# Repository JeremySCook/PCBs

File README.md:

# PCBs
Circuit boards designed by Jeremy Cook

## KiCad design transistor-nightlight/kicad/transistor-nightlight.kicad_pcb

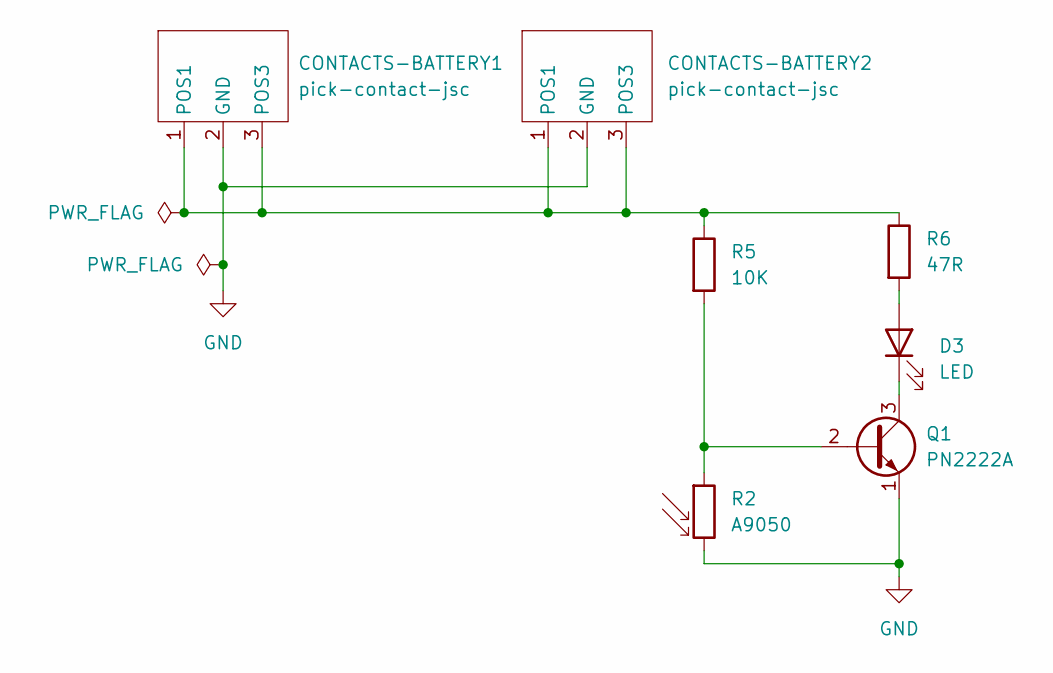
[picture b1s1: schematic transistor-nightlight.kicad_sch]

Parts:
CONTACTS-BATTERY1, CONTACTS-BATTERY2: pick-contact-jsc; pick-battery-jsc
D3: LED; LED_D3.0mm
Q1: PN2222A; TO-92_Inline
R2: A9050; R_LDR_5.0x4.1mm_P3mm_Vertical
R5: 10K; R_Axial_DIN0204_L3.6mm_D1.6mm_P2.54mm_Vertical
R6: 47R; R_Axial_DIN0204_L3.6mm_D1.6mm_P2.54mm_Vertical

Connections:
GND: CONTACTS-BATTERY1.2 (GND), CONTACTS-BATTERY2.2 (GND), Q1.1 (E), R2.2
unnamed: CONTACTS-BATTERY1.1 (POS1), CONTACTS-BATTERY1.3 (POS3), CONTACTS-BATTERY2.1 (POS1), CONTACTS-BATTERY2.3 (POS3), R5.1, R6.1
unnamed: D3.2 (A), R6.2
unnamed: D3.1 (K), Q1.3 (C)
unnamed: Q1.2 (B), R2.1, R5.2

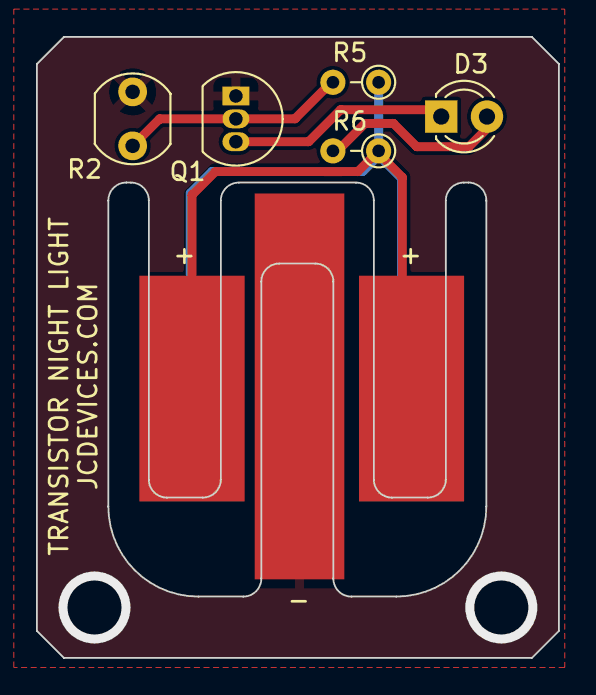
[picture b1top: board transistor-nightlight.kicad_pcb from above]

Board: 2 copper layers, 29.0 x 34.5 mm, 7 parts (1 on the bottom side), 5 nets.

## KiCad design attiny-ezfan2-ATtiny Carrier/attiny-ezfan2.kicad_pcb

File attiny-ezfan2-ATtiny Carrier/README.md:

Simple ATtiny85/45/25 breakout

Originally available on Tindie: https://www.tindie.com/products/27207 - now retired

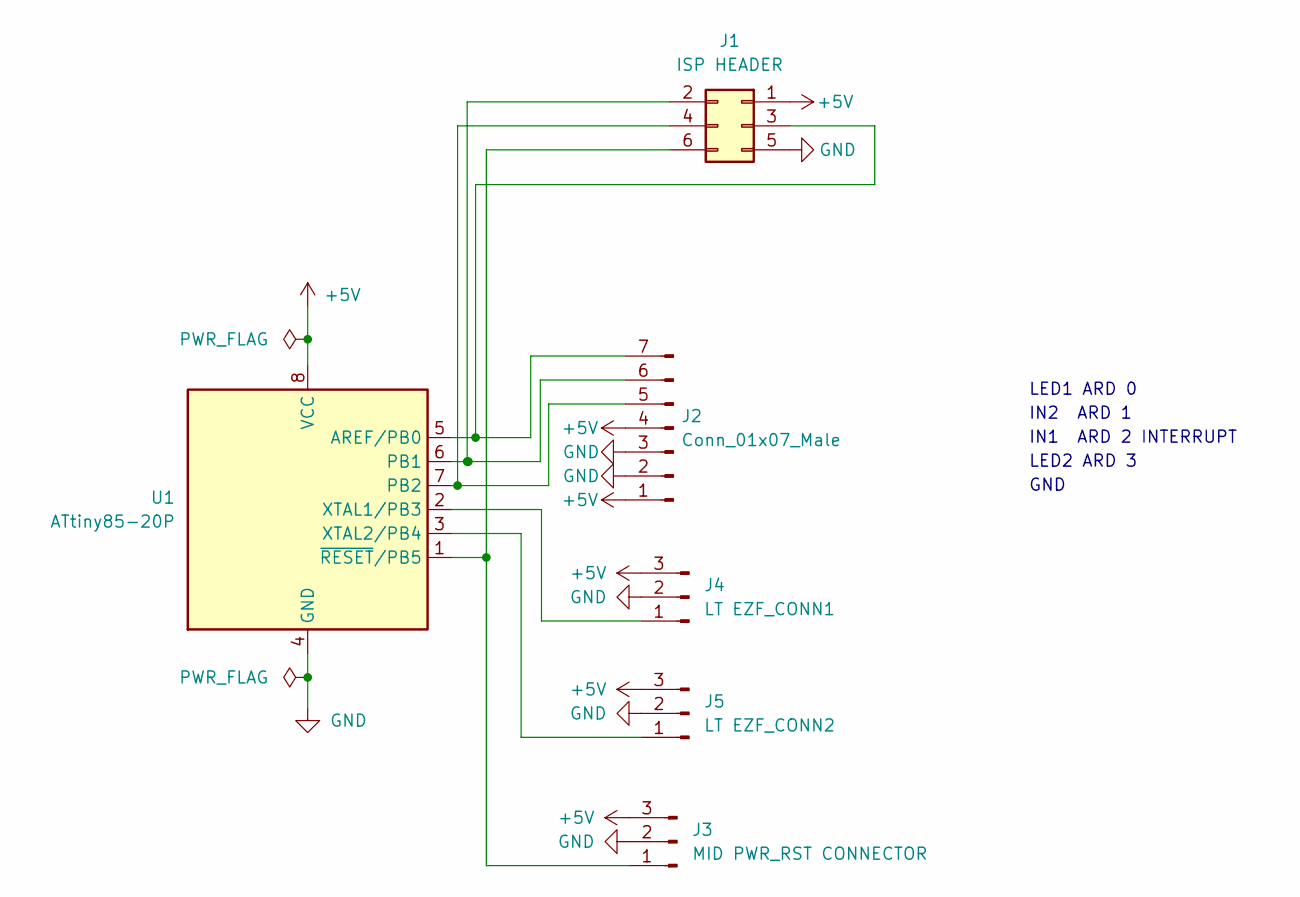
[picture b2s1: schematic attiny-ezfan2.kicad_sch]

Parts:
J1: ISP HEADER; PinSocket_2x03_P2.54mm_Vertical
J2: Conn_01x07_Male; PinSocket_1x07_P2.54mm_Vertical
J3: MID PWR_RST CONNECTOR; PinHeader_1x03_P2.54mm_Vertical
J4: LT EZF_CONN1; PinHeader_1x03_P2.54mm_Vertical
J5: LT EZF_CONN2; PinHeader_1x03_P2.54mm_Vertical
U1: ATtiny85-20P; DIP-8_W7.62mm

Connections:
+5V: J1.1, J2.1, J2.4, J3.3, J4.3, J5.3, U1.8 (VCC)
GND: J1.5, J2.2, J2.3, J3.2, J4.2, J5.2, U1.4 (GND)
unnamed: J1.2, J2.6, U1.6 (PB1)
unnamed: J1.3, J2.7, U1.5 (AREF/PB0)
unnamed: J1.4, J2.5, U1.7 (PB2)
unnamed: J1.6, J3.1, U1.1 (~RESET/PB5)
unnamed: J4.1, U1.2 (XTAL1/PB3)
unnamed: J5.1, U1.3 (XTAL2/PB4)

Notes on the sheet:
LED1 ARD 0
IN1 ARD 2 INTERRUPT
GND
IN2 ARD 1
LED2 ARD 3

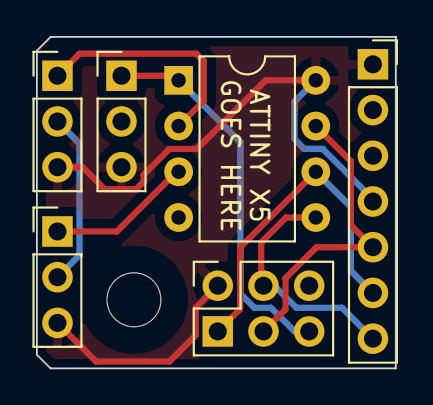
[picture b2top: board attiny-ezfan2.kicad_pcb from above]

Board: 2 copper layers, 19.9 x 18.4 mm, 6 parts (0 on the bottom side), 8 nets.

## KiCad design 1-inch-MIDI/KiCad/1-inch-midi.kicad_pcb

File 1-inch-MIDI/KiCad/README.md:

KiCad Backup as of Aug 6th 2024

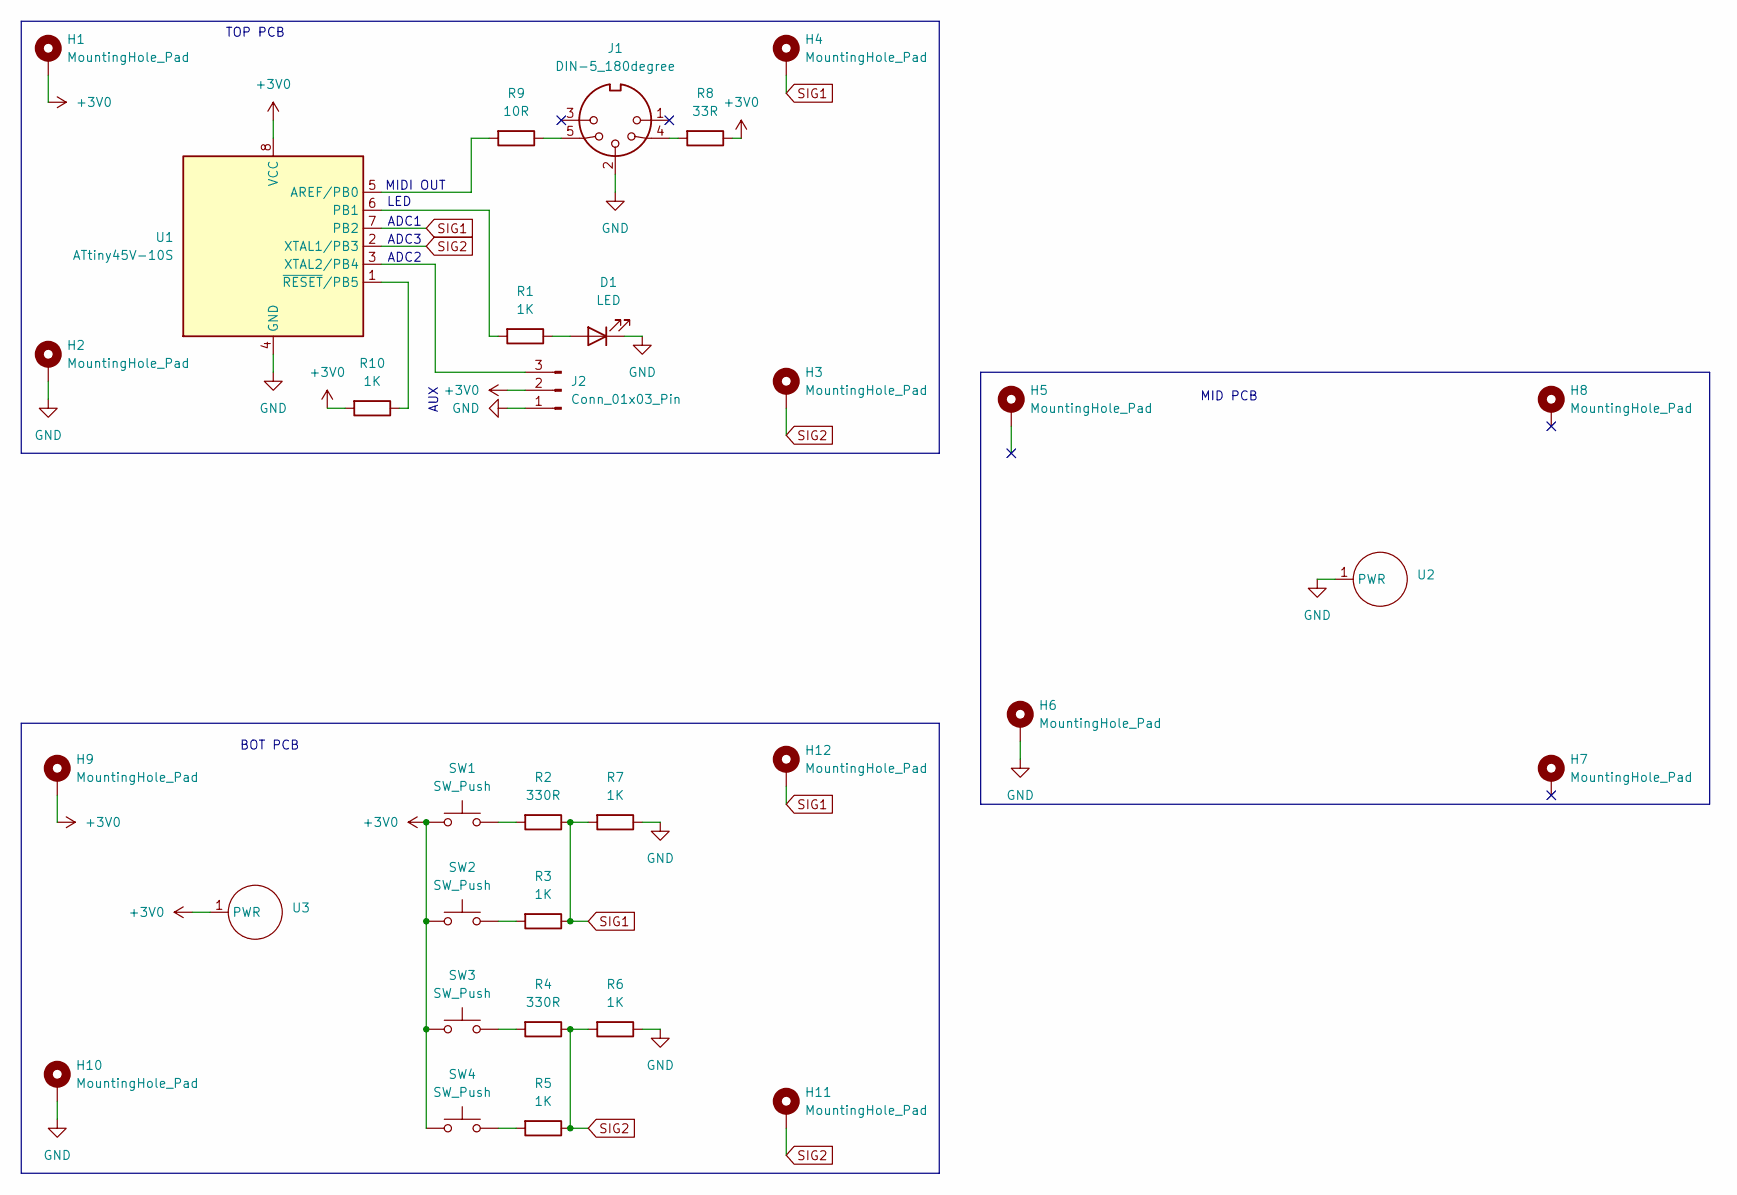
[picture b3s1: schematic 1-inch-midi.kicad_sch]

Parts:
D1: LED; LED_0805_2012Metric_Pad1.15x1.40mm_HandSolder
H1, H2, H3, H4, H5, H6, H7, H8, H9, H10, H11, H12: MountingHole_Pad; MountingHole_2.5mm_Pad_TopBottom
J1: DIN-5_180degree; CONN-TH_DIN-504-M10
J2: Conn_01x03_Pin; PinHeader_1x03_P2.54mm_Vertical
R1, R3, R5, R6, R7, R10: 1K; R_0805_2012Metric_Pad1.20x1.40mm_HandSolder
R2, R4: 330R; R_0805_2012Metric_Pad1.20x1.40mm_HandSolder
R8: 33R; R_0805_2012Metric_Pad1.20x1.40mm_HandSolder
R9: 10R; R_0805_2012Metric_Pad1.20x1.40mm_HandSolder
SW1, SW2, SW3, SW4: SW_Push; SW_SPST_EVPBF
U1: ATtiny45V-10S; SOIC-8W_5.3x5.3mm_P1.27mm
U2, U3: CR2032

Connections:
+3V0: H1.1, H9.1, J2.2, R8.1, R10.2, SW1.1, SW2.1, SW3.1, SW4.1, U1.8 (VCC), U3.1 (PWR)
GND: D1.1 (K), H2.1, H6.1, H10.1, J1.2, J2.1, R6.1, R7.1, U1.4 (GND), U2.1 (PWR)
unnamed: D1.2 (A), R1.1
unnamed: J1.4, R8.2
unnamed: J1.5, R9.1
unnamed: J2.3, U1.3 (XTAL2/PB4)
unnamed: R2.2, SW1.2
unnamed: R3.2, SW2.2
unnamed: R4.2, SW3.2
unnamed: R5.2, SW4.2
unnamed: R9.2, U1.5 (AREF/PB0)
unnamed: R1.2, U1.6 (PB1)
unnamed: R10.1, U1.1 (~RESET/PB5)
SIG1: H4.1, H12.1, R2.1, R3.1, R7.2, U1.7 (PB2)
SIG2: H3.1, H11.1, R4.1, R5.1, R6.2, U1.2 (XTAL1/PB3)

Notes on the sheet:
BOT PCB
LED
AUX
MID PCB
ADC2
MIDI OUT
ADC1
ADC3
TOP PCB

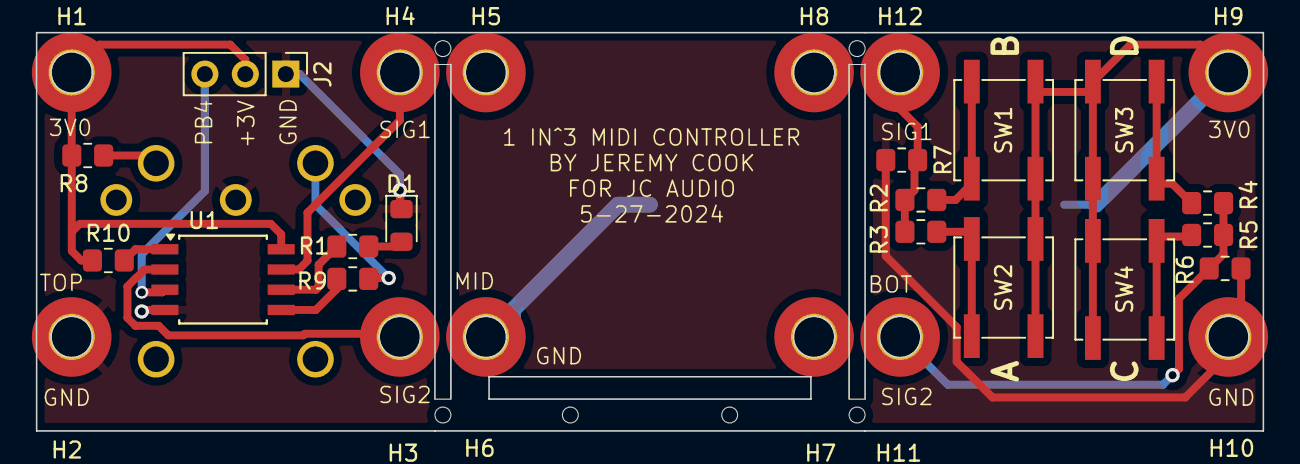
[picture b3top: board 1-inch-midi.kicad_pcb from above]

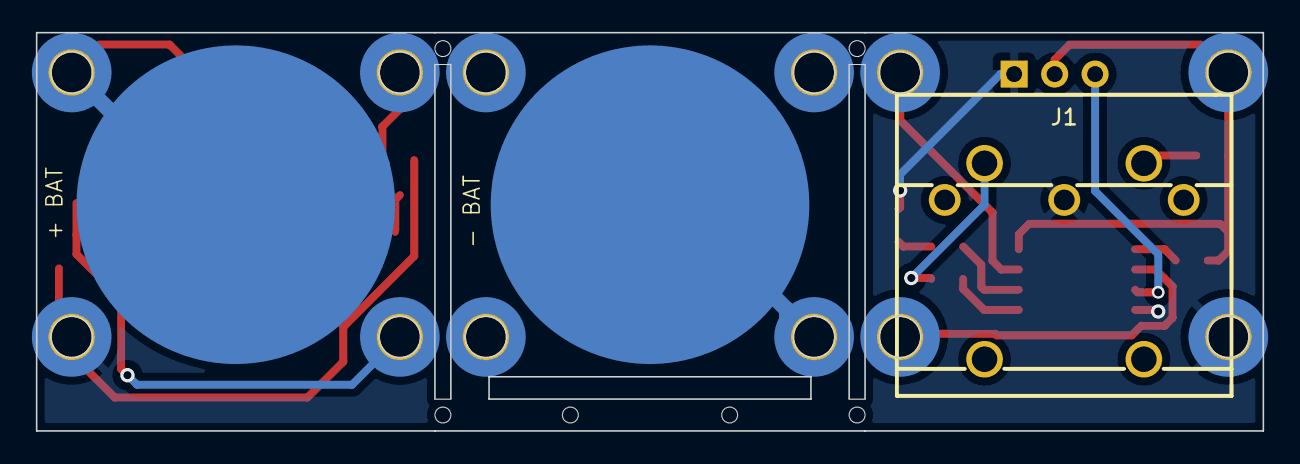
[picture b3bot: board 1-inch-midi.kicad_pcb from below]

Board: 2 copper layers, 77.0 x 25.0 mm, 32 parts (3 on the bottom side), 15 nets.

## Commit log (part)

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2026-03-04 Create LICENSE
